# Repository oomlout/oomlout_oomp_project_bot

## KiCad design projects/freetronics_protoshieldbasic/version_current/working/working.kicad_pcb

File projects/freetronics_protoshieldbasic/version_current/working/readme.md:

# ProtoShieldBasic by freetronics  
This is a harvested standardized copy of a project from github.  
The original project can be found at:  
https://github.com/freetronics/ProtoShieldBasic  
Please consult that link for additional, details, files, and license information.  
Note: It was auto harvested and if the original repo had more than one board file or anything out of the ordinary the files here are likely not representative.

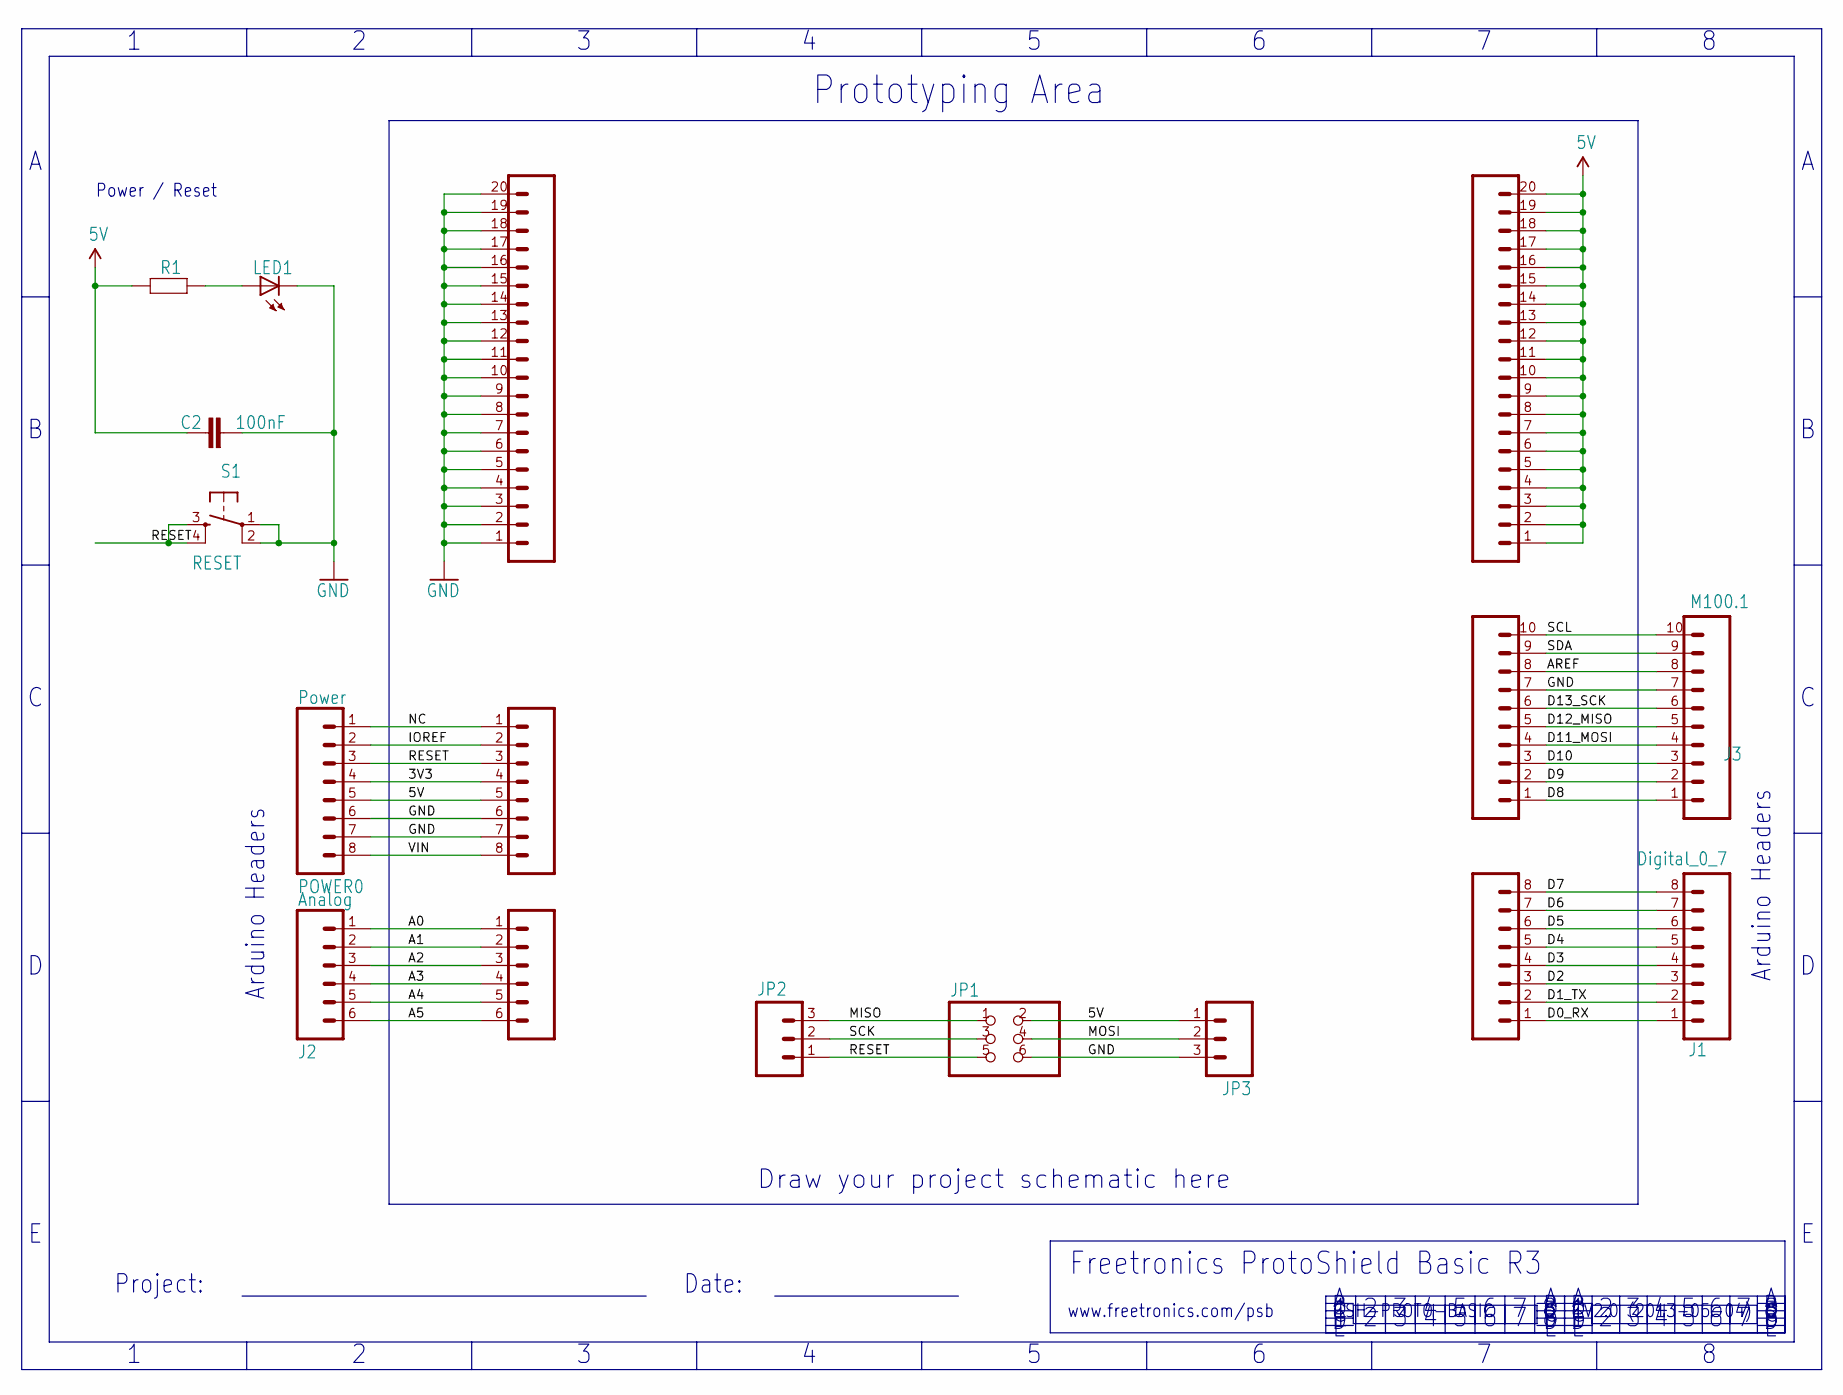
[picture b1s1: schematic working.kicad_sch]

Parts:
C2: 100nF; CAP-PTH-SMALL
J1: Digital_0_7; 1X08
J2: Analog; 1X06
J3: M100.1; 1X10
JP1: PINHD-2X3; 2X03
JP2, JP3: M03PTH; 1X03
LED1: LED3MM
PADS_5V0: M20; 1X20
PADS_GND0: M20; 1X20
POWER0: Power; 1X08
R1: RESISTORPTH1; AXIAL-0.3
S1: RESET; TACTILE-PTH
SL1: Digital_0_7; 1X08
SL2: Analog; 1X06
SL3: M100.1; 1X10
SLP0: Power; 1X08

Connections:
3V3: POWER0.4, SLP0.4
5V: C2.1, JP1.2, JP3.1, PADS_5V0.1, PADS_5V0.2, PADS_5V0.3, PADS_5V0.4, PADS_5V0.5, PADS_5V0.6, PADS_5V0.7, PADS_5V0.8, PADS_5V0.9, PADS_5V0.10, PADS_5V0.11, PADS_5V0.12, PADS_5V0.13, PADS_5V0.14, PADS_5V0.15, PADS_5V0.16, PADS_5V0.17, PADS_5V0.18, PADS_5V0.19, PADS_5V0.20, POWER0.5, R1.P$1 (1), SLP0.5
A0: J2.1, SL2.1
A1: J2.2, SL2.2
A2: J2.3, SL2.3
A3: J2.4, SL2.4
A4: J2.5, SL2.5
A5: J2.6, SL2.6
AREF: J3.8, SL3.8
D0_RX: J1.1, SL1.1
D1_TX: J1.2, SL1.2
D2: J1.3, SL1.3
D3: J1.4, SL1.4
D4: J1.5, SL1.5
D5: J1.6, SL1.6
D6: J1.7, SL1.7
D7: J1.8, SL1.8
D8: J3.1, SL3.1
D9: J3.2, SL3.2
D10: J3.3, SL3.3
D11_MOSI: J3.4, SL3.4
D12_MISO: J3.5, SL3.5
D13_SCK: J3.6, SL3.6
GND: C2.2, J3.7, JP1.6, JP3.3, LED1.K (C), PADS_GND0.1, PADS_GND0.2, PADS_GND0.3, PADS_GND0.4, PADS_GND0.5, PADS_GND0.6, PADS_GND0.7, PADS_GND0.8, PADS_GND0.9, PADS_GND0.10, PADS_GND0.11, PADS_GND0.12, PADS_GND0.13, PADS_GND0.14, PADS_GND0.15, PADS_GND0.16, PADS_GND0.17, PADS_GND0.18, PADS_GND0.19, PADS_GND0.20, POWER0.6, POWER0.7, S1.1, S1.2, SL3.7, SLP0.6, SLP0.7
IOREF: POWER0.2, SLP0.2
MISO: JP1.1, JP2.3
MOSI: JP1.4, JP3.2
unnamed: LED1.A, R1.P$2 (2)
NC: POWER0.1, SLP0.1
RESET: JP1.5, JP2.1, POWER0.3, S1.3, S1.4, SLP0.3
SCK: JP1.3, JP2.2
SCL: J3.10, SL3.10
SDA: J3.9, SL3.9
VIN: POWER0.8, SLP0.8

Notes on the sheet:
Date:
Prototyping Area
Project:
V2.0 (2013-05-04)
Arduino Headers
www.freetronics.com/psb
Draw your project schematic here
SH-PROTO-BASIC
Freetronics ProtoShield Basic R3
Power / Reset

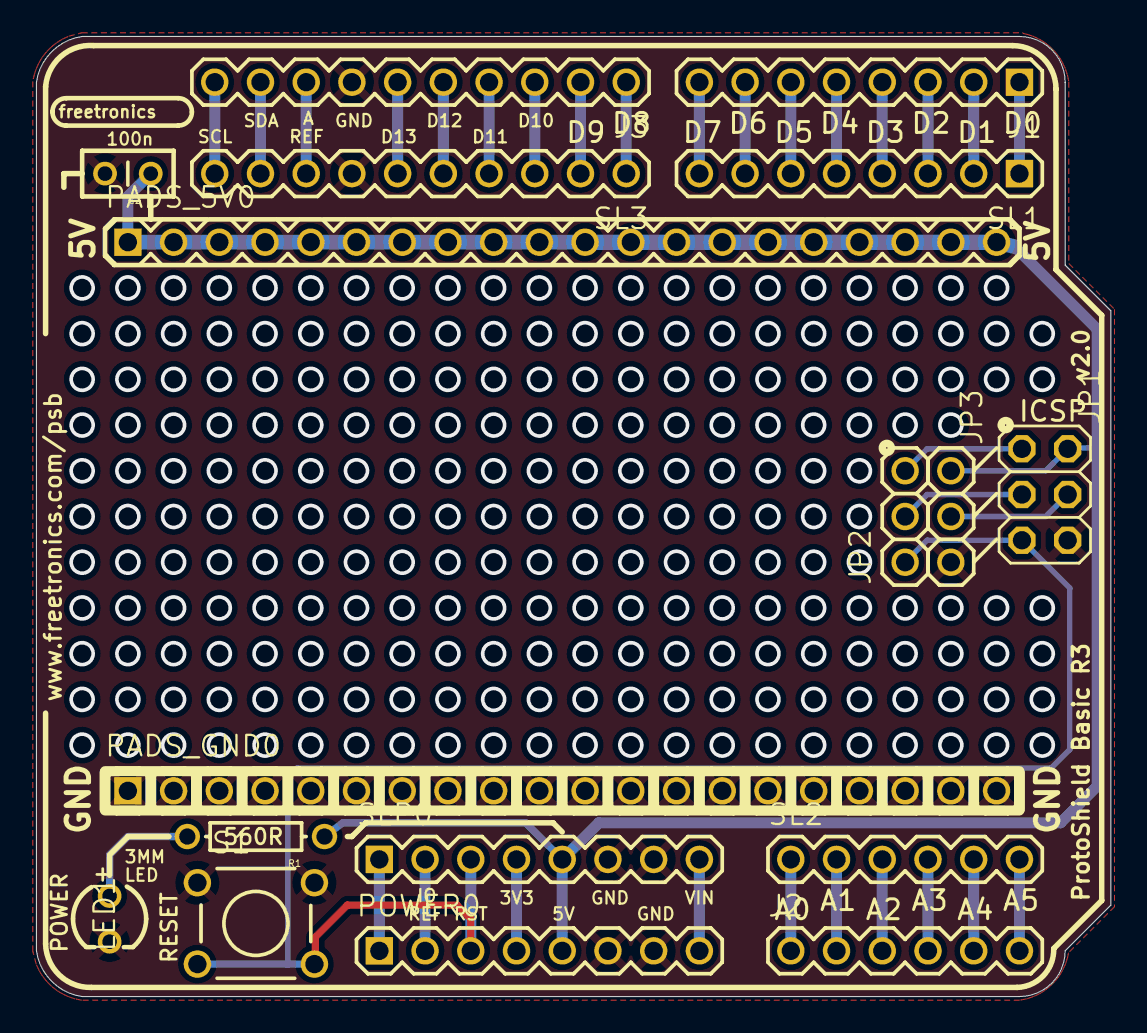
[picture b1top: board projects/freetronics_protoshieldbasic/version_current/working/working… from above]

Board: 2 copper layers, 59.7 x 53.3 mm, 17 parts (0 on the bottom side), 34 nets.

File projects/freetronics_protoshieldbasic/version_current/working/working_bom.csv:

"Id";"Designator";"Footprint";"Quantity";"Designation";"Supplier and ref";
1;"LED1";"LED3MM";1;"";;;
2;"SL2,J2";"1X06";2;"Analog";;;
3;"J1,SL1";"1X08";2;"Digital_0_7";;;
4;"PADS_GND0,PADS_5V0";"1X20";2;"M20";;;
5;"S1";"TACTILE-PTH";1;"RESET";;;
6;"SLP0,POWER0";"1X08";2;"Power";;;
7;"SL3,J3";"1X10";2;"Digital_8_13";;;
8;"C2";"CAP-PTH-SMALL";1;"100nF";;;
9;"JP3,JP2";"1X03";2;"";;;
10;"JP1";"2X03";1;"";;;
11;"R1";"AXIAL-0.3";1;"";;;

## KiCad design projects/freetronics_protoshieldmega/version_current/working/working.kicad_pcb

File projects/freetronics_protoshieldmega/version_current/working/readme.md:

# ProtoShieldMega by freetronics  
This is a harvested standardized copy of a project from github.  
The original project can be found at:  
https://github.com/freetronics/ProtoShieldMega  
Please consult that link for additional, details, files, and license information.  
Note: It was auto harvested and if the original repo had more than one board file or anything out of the ordinary the files here are likely not representative.

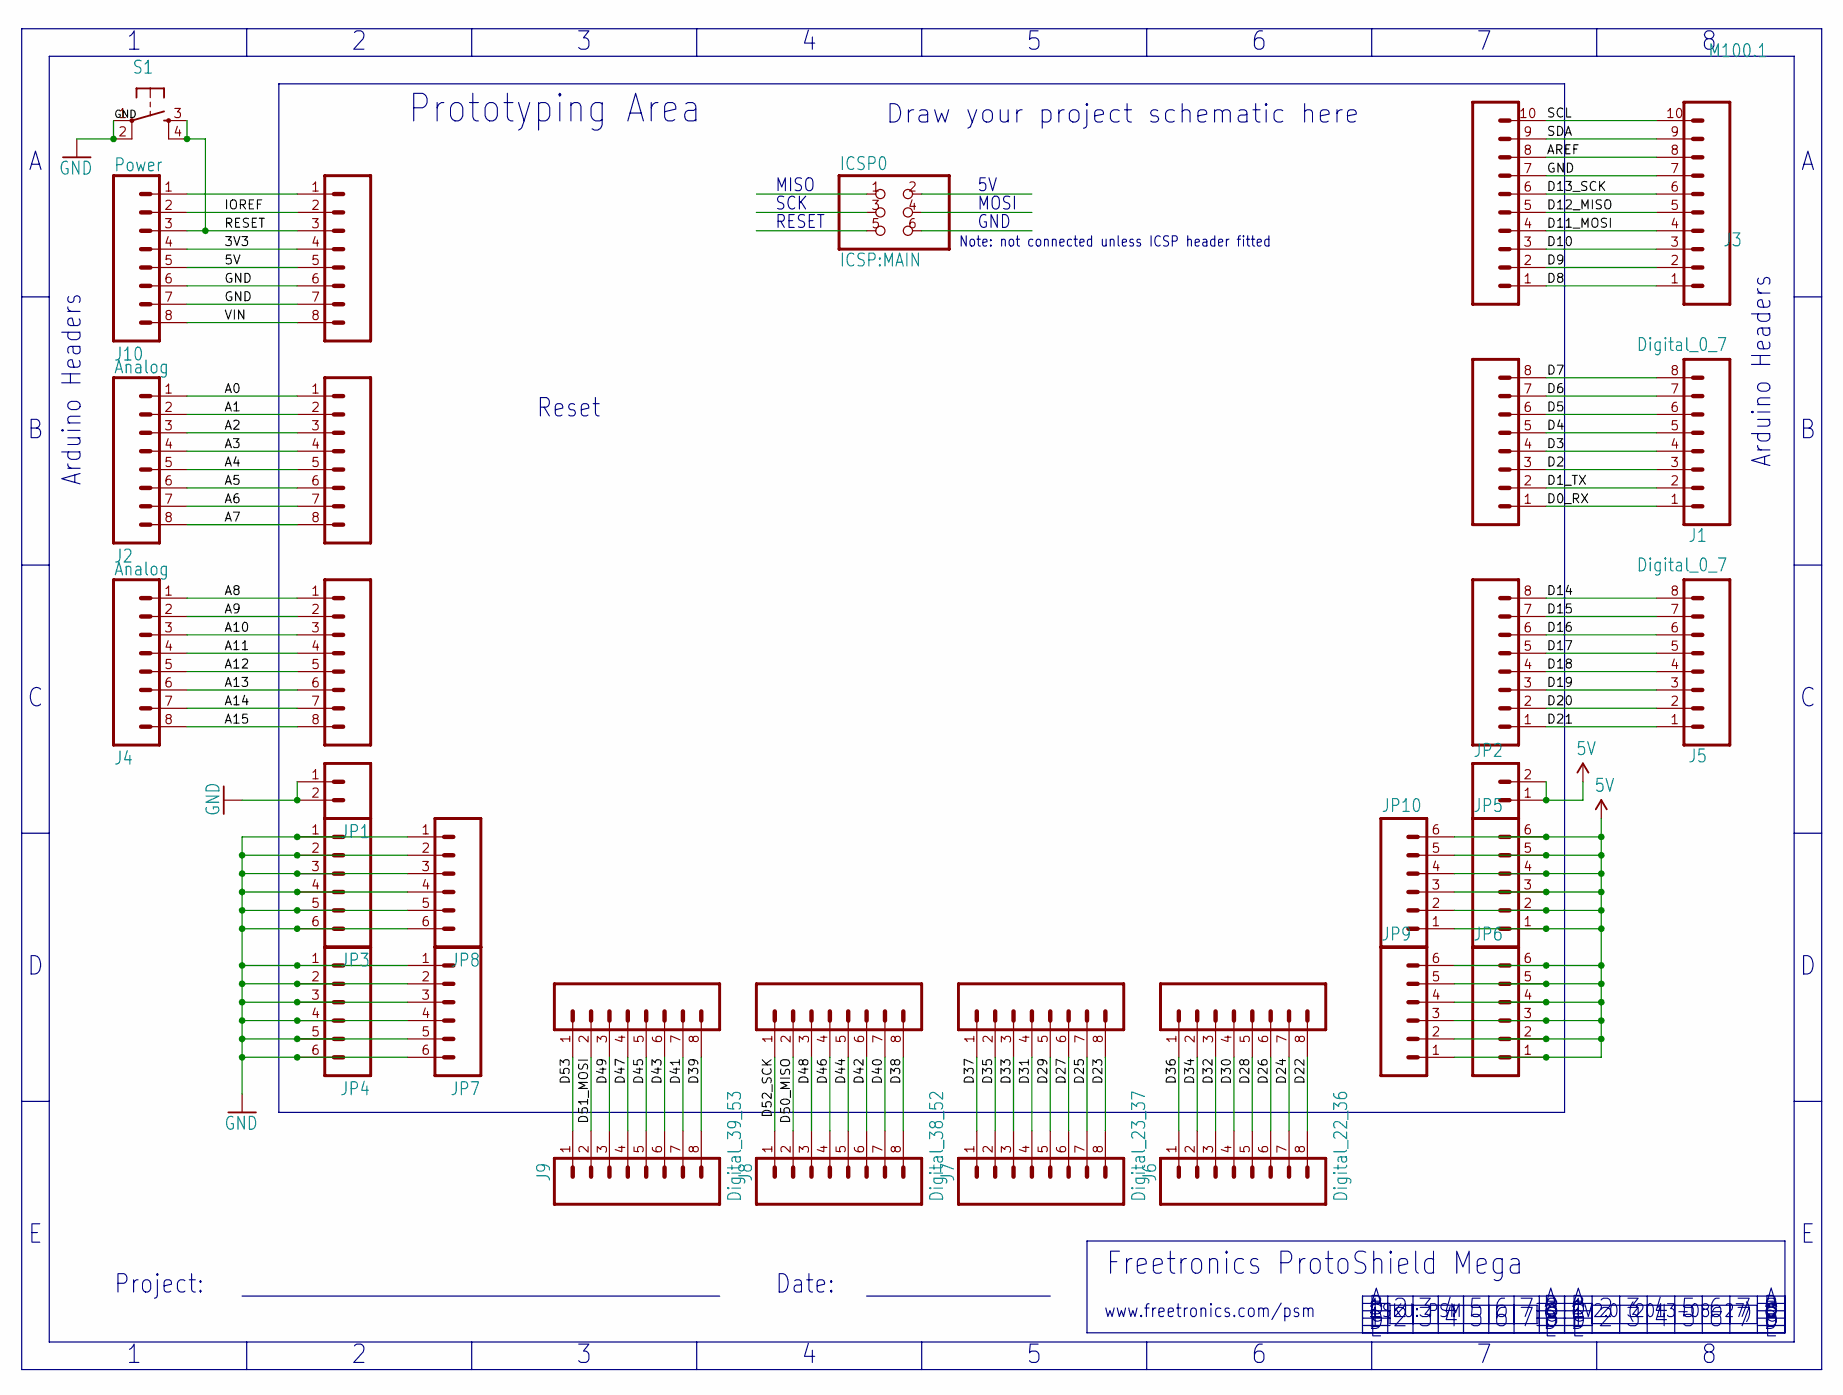
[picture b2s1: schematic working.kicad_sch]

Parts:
ICSP0: ICSP:MAIN; 2X03
J1, J5: Digital_0_7; 1X08
J2, J4: Analog; 1X08
J3: M100.1; 1X10
J6: Digital_22_36; 1X08
J7: Digital_23_37; 1X08
J8: Digital_38_52; 1X08
J9: Digital_39_53; 1X08
J10: Power; 1X08
JP1, JP2: M02PTH; 1X02
JP3, JP4, JP5, JP6, JP7, JP8, JP9, JP10: M06SIP; 1X06
S1: TAC_SWITCHPTH; TACTILE-PTH
SL1, SL5, SL6, SL7, SL8, SL9: Digital_0_7; 1X08
SL2, SL4: Analog; 1X08
SL3: M100.1; 1X10
SLP0: Power; 1X08

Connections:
3V3: J10.4, SLP0.4
5V: J10.5, JP2.1, JP2.2, JP5.1, JP5.2, JP5.3, JP5.4, JP5.5, JP5.6, JP6.1, JP6.2, JP6.3, JP6.4, JP6.5, JP6.6, JP9.1, JP9.2, JP9.3, JP9.4, JP9.5, JP9.6, JP10.1, JP10.2, JP10.3, JP10.4, JP10.5, JP10.6, SLP0.5
A0: J2.1, SL2.1
A1: J2.2, SL2.2
A2: J2.3, SL2.3
A3: J2.4, SL2.4
A4: J2.5, SL2.5
A5: J2.6, SL2.6
A6: J2.7, SL2.7
A7: J2.8, SL2.8
A8: J4.1, SL4.1
A9: J4.2, SL4.2
A10: J4.3, SL4.3
A11: J4.4, SL4.4
A12: J4.5, SL4.5
A13: J4.6, SL4.6
A14: J4.7, SL4.7
A15: J4.8, SL4.8
AREF: J3.8, SL3.8
D0_RX: J1.1, SL1.1
D1_TX: J1.2, SL1.2
D2: J1.3, SL1.3
D3: J1.4, SL1.4
D4: J1.5, SL1.5
D5: J1.6, SL1.6
D6: J1.7, SL1.7
D7: J1.8, SL1.8
D8: J3.1, SL3.1
D9: J3.2, SL3.2
D10: J3.3, SL3.3
D11_MOSI: J3.4, SL3.4
D12_MISO: J3.5, SL3.5
D13_SCK: J3.6, SL3.6
D14: J5.8, SL5.8
D15: J5.7, SL5.7
D16: J5.6, SL5.6
D17: J5.5, SL5.5
D18: J5.4, SL5.4
D19: J5.3, SL5.3
D20: J5.2, SL5.2
D21: J5.1, SL5.1
D22: J6.8, SL6.8
D23: J7.8, SL7.8
D24: J6.7, SL6.7
D25: J7.7, SL7.7
D26: J6.6, SL6.6
D27: J7.6, SL7.6
D28: J6.5, SL6.5
D29: J7.5, SL7.5
D30: J6.4, SL6.4
D31: J7.4, SL7.4
D32: J6.3, SL6.3
D33: J7.3, SL7.3
D34: J6.2, SL6.2
D35: J7.2, SL7.2
D36: J6.1, SL6.1
D37: J7.1, SL7.1
D38: J8.8, SL8.8
D39: J9.8, SL9.8
D40: J8.7, SL8.7
D41: J9.7, SL9.7
D42: J8.6, SL8.6
D43: J9.6, SL9.6
D44: J8.5, SL8.5
D45: J9.5, SL9.5
D46: J8.4, SL8.4
D47: J9.4, SL9.4
D48: J8.3, SL8.3
D49: J9.3, SL9.3
D50_MISO: J8.2, SL8.2
D51_MOSI: J9.2, SL9.2
D52_SCK: J8.1, SL8.1
D53: J9.1, SL9.1
GND: J3.7, J10.6, J10.7, JP1.1, JP1.2, JP3.1, JP3.2, JP3.3, JP3.4, JP3.5, JP3.6, JP4.1, JP4.2, JP4.3, JP4.4, JP4.5, JP4.6, JP7.1, JP7.2, JP7.3, JP7.4, JP7.5, JP7.6, JP8.1, JP8.2, JP8.3, JP8.4, JP8.5, JP8.6, S1.1, S1.2, SL3.7, SLP0.6, SLP0.7
IOREF: J10.2, SLP0.2
unnamed: J10.1, SLP0.1
RESET: J10.3, S1.3, S1.4, SLP0.3
SCL: J3.10, SL3.10
SDA: J3.9, SL3.9
VIN: J10.8, SLP0.8

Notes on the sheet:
www.freetronics.com/psm
V2.0 (2013-08-27)
Note: not connected unless ICSP header fitted
RESET
MISO
Arduino Headers
GND
Reset
Prototyping Area
Freetronics ProtoShield Mega
MOSI
SKU: PSM
Draw your project schematic here
Project:
SCK
Date:

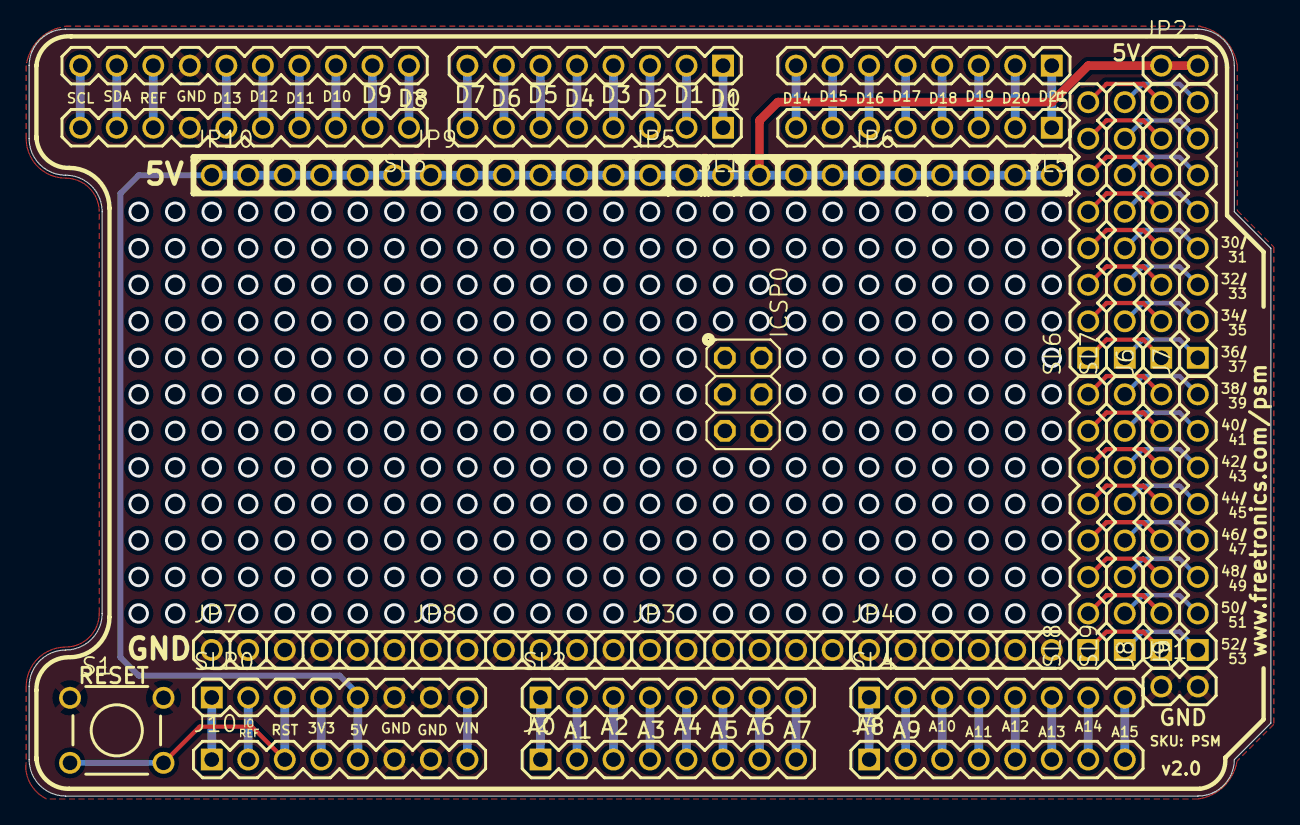
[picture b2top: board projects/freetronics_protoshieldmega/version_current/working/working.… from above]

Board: 2 copper layers, 86.4 x 53.3 mm, 32 parts (0 on the bottom side), 80 nets.

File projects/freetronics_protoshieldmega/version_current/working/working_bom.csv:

"Id";"Designator";"Footprint";"Quantity";"Designation";"Supplier and ref";
1;"JP4,JP9,JP5,JP8,JP6,JP10,JP7,JP3";"1X06";8;"";;;
2;"SL9,SL7,SL8,SL1,SL5,J5,J1,SL6";"1X08";8;"Digital_0_7";;;
3;"J2,J4,SL4,SL2";"1X08";4;"Analog";;;
4;"J3,SL3";"1X10";2;"Digital_8_13";;;
5;"S1";"TACTILE-PTH";1;"";;;
6;"ICSP0";"2X03";1;"ICSP:MAIN";;;
7;"J8";"1X08";1;"Digital_38_52";;;
8;"JP2,JP1";"1X02";2;"";;;
9;"J7";"1X08";1;"Digital_23_37";;;
10;"J9";"1X08";1;"Digital_39_53";;;
11;"SLP0,J10";"1X08";2;"Power";;;
12;"J6";"1X08";1;"Digital_22_36";;;

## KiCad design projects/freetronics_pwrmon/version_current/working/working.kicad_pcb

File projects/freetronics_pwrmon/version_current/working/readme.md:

# PWRMON by freetronics  
This is a harvested standardized copy of a project from github.  
The original project can be found at:  
https://github.com/freetronics/PWRMON  
Please consult that link for additional, details, files, and license information.  
Note: It was auto harvested and if the original repo had more than one board file or anything out of the ordinary the files here are likely not representative.

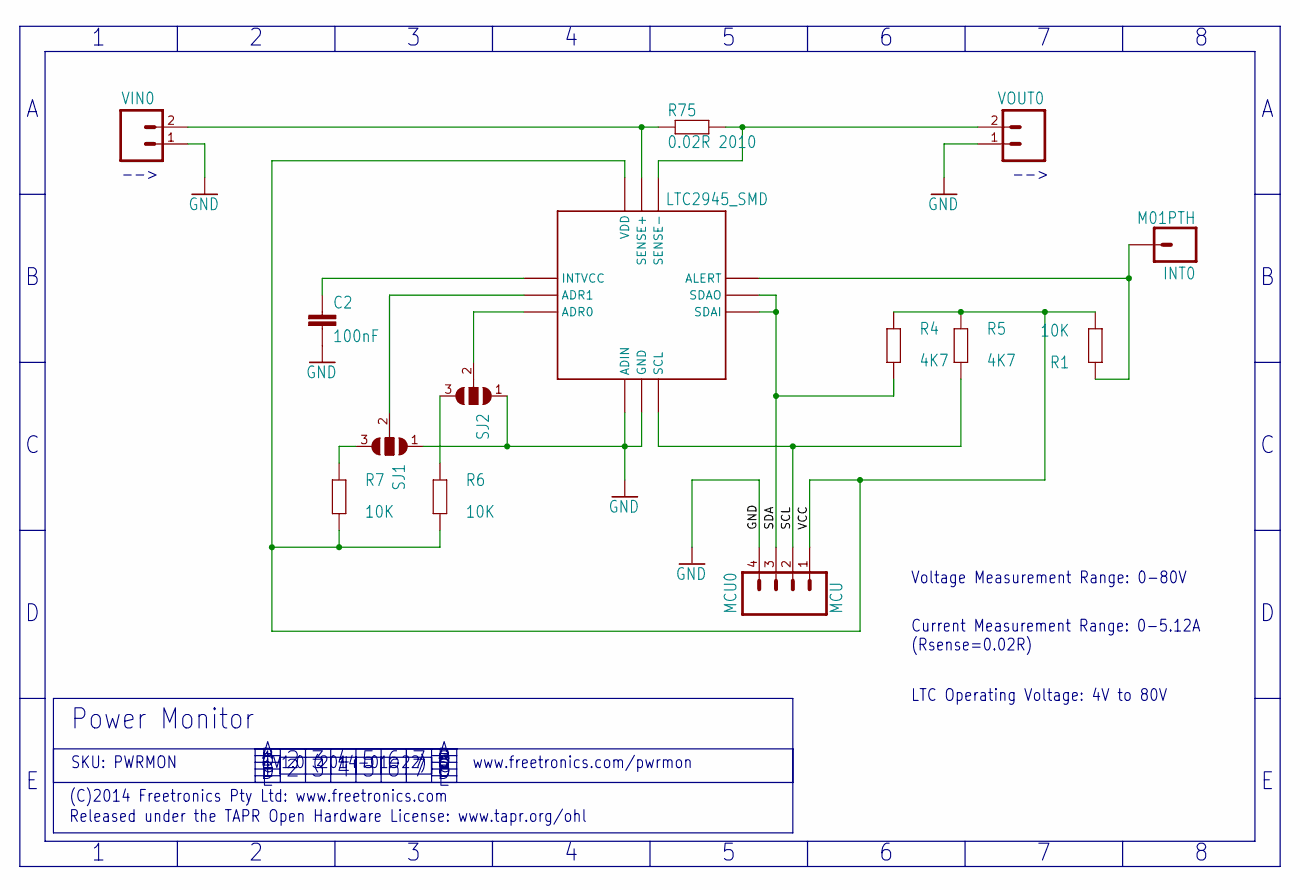
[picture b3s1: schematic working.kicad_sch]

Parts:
C2: 100nF; 0603
INT0: M01PTH; 1X01
LTC2945: LTC2945_SMD; QFN-12
MCU0: MCU; 1X04
R1, R6, R7: 10K; 0603
R4, R5: 4K7; 0603
R75: 0.02R 2010; R2010
SJ1, SJ2: SJ2W; SJ_2
VIN0: M02PTH; 1X02
VOUT0: M02PTH; 1X02

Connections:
GND: C2.2, LTC2945.4 (ADIN), LTC2945.5 (GND), MCU0.4, SJ1.1, SJ2.1, VIN0.1, VOUT0.1
unnamed: LTC2945.11 (SENSE+), R75.1, VIN0.2
unnamed: LTC2945.10 (SENSE-), R75.2, VOUT0.2
unnamed: LTC2945.2 (ADR1), SJ1.2
unnamed: INT0.1, LTC2945.9 (ALERT), R1.2
unnamed: C2.1, LTC2945.1 (INTVCC)
unnamed: LTC2945.3 (ADR0), SJ2.2
unnamed: R7.2, SJ1.3
unnamed: R6.2, SJ2.3
SCL: LTC2945.6 (SCL), MCU0.2, R5.1
SDA: LTC2945.7 (SDAI), LTC2945.8 (SDAO), MCU0.3, R4.1
VCC: LTC2945.12 (VDD), MCU0.1, R1.1, R4.2, R5.2, R6.1, R7.1

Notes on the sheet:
www.freetronics.com/pwrmon
Voltage Measurement Range: 0-80V
(C)2014 Freetronics Pty Ltd: www.freetronics.com
Power Monitor
Current Measurement Range: 0-5.12A (Rsense=0.02R)
SKU: PWRMON
Released under the TAPR Open Hardware License: www.tapr.org/ohl
-->
LTC Operating Voltage: 4V to 80V
V1.0 (2014-01-22)

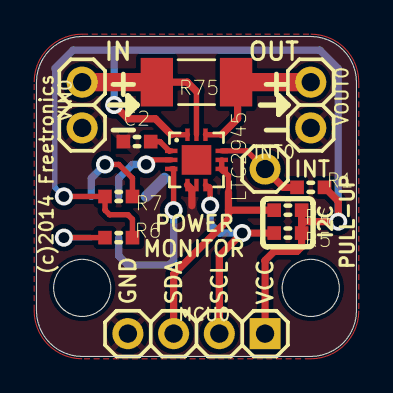
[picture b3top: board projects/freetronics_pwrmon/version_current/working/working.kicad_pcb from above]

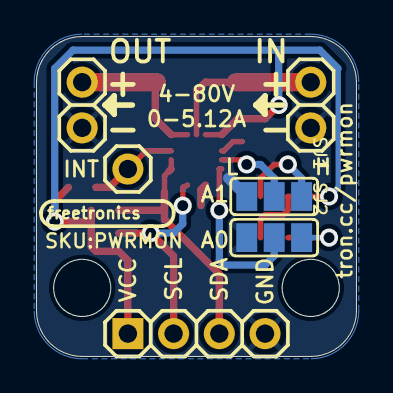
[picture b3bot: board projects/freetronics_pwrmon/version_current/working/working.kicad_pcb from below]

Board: 2 copper layers, 17.8 x 17.8 mm, 16 parts (2 on the bottom side), 12 nets.

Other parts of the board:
@HOLE0, @HOLE1: (no value)

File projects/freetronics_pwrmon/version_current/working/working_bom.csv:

"Id";"Designator";"Footprint";"Quantity";"Designation";"Supplier and ref";
1;"R7,R1,R6";"0603";3;"10K";;;
2;"C2";"0603";1;"100nF";;;
3;"@HOLE1,@HOLE0";"";2;"";;;
4;"INT0";"1X01";1;"M01PTH";;;
5;"VIN0,VOUT0";"1X02";2;"";;;
6;"R4,R5";"0603";2;"4K7";;;
7;"R75";"R2010";1;"0.02R 2010";;;
8;"MCU0";"1X04";1;"MCU";;;
9;"LTC2945";"QFN-12";1;"LTC2945_SMD";;;
10;"SJ2,SJ1";"SJ_2";2;"";;;

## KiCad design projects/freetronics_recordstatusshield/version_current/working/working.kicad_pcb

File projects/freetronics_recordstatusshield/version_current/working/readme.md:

# RecordStatusShield by freetronics  
This is a harvested standardized copy of a project from github.  
The original project can be found at:  
https://github.com/freetronics/RecordStatusShield  
Please consult that link for additional, details, files, and license information.  
Note: It was auto harvested and if the original repo had more than one board file or anything out of the ordinary the files here are likely not representative.

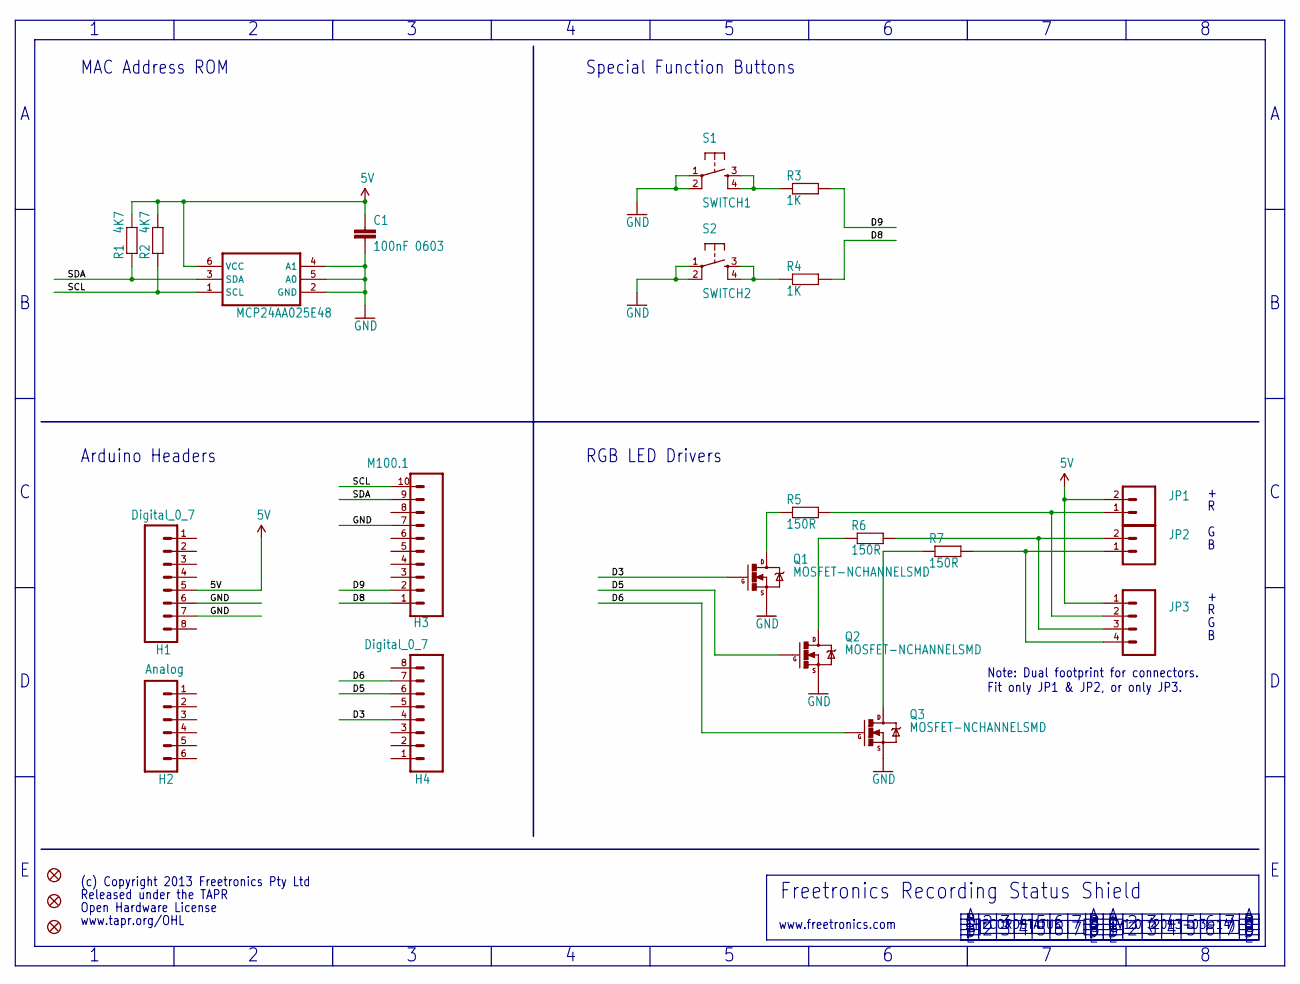
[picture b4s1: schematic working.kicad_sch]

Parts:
C1: 100nF 0603; C0603
FID5, FID6, FID7: FIDUCIAL1X2.5; FIDUCIAL-1X2.5
H1, H4: Digital_0_7; 1X08
H2: Analog; 1X06
H3: M100.1; 1X10
IC1: MCP24AA025E48; SOT23-6
JP1, JP2: M025MM; SCREWTERMINAL-5MM-2
JP3: M04PTH; 1X04
Q1, Q2, Q3: MOSFET-NCHANNELSMD; SOT23-3
R1, R2: 4K7; 0603
R3, R4: 1K; 0603
R5, R6, R7: 150R; 0603
S1: SWITCH1; TACTILE-PTH
S2: SWITCH2; TACTILE-PTH

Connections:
5V: C1.1, H1.5, IC1.6 (VCC), JP1.2, JP3.1, R1.2, R2.2
D3: H4.4, Q1.1 (G)
D5: H4.6, Q2.1 (G)
D6: H4.7, Q3.1 (G)
D8: H3.1, R4.2
D9: H3.2, R3.2
GND: C1.2, H1.6, H1.7, H3.7, IC1.2 (GND), IC1.4 (A1), IC1.5 (A0), Q1.2 (S), Q2.2 (S), Q3.2 (S), S1.1, S1.2, S2.1, S2.2
unnamed: R3.1, S1.3, S1.4
unnamed: R4.1, S2.3, S2.4
unnamed: JP2.1, JP3.4, R7.2
unnamed: JP2.2, JP3.3, R6.2
unnamed: JP1.1, JP3.2, R5.2
unnamed: Q1.3 (D), R5.1
unnamed: Q2.3 (D), R6.1
unnamed: Q3.3 (D), R7.1
SCL: H3.10, IC1.1 (SCL), R2.1
SDA: H3.9, IC1.3 (SDA), R1.1

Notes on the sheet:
Special Function Buttons
V1.0 (2013-03-14)
www.freetronics.com
Open Hardware License
Note: Dual footprint for connectors. Fit only JP1 & JP2, or only JP3.
Arduino Headers
(c) Copyright 2013 Freetronics Pty Ltd
Released under the TAPR
RECORDSTATUS
MAC Address ROM
Freetronics Recording Status Shield
RGB LED Drivers
www.tapr.org/OHL

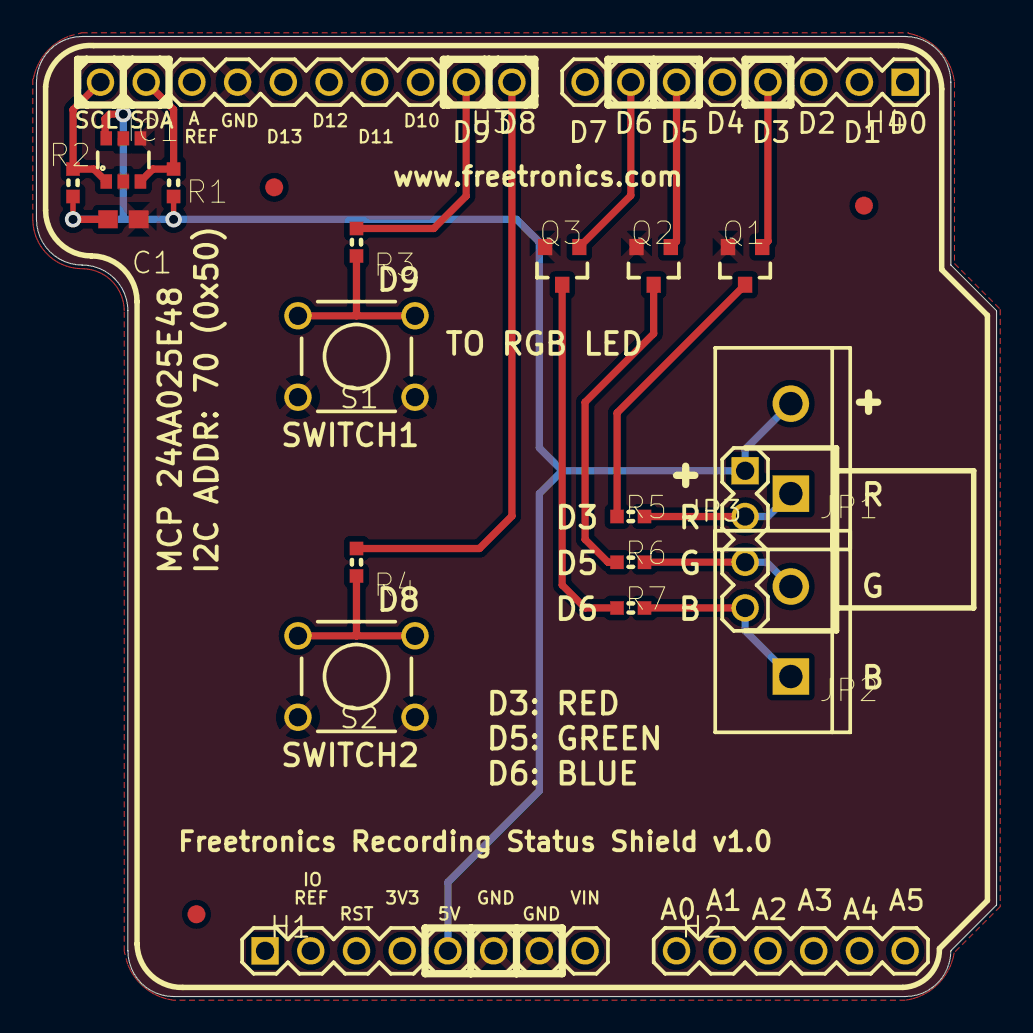
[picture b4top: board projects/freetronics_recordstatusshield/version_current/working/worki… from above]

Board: 2 copper layers, 53.3 x 53.3 mm, 24 parts (0 on the bottom side), 17 nets.

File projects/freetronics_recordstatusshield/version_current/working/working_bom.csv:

"Id";"Designator";"Footprint";"Quantity";"Designation";"Supplier and ref";
1;"R5,R6,R7";"0603";3;"150R";;;
2;"R1,R2";"0603";2;"4K7";;;
3;"Q3,Q2,Q1";"SOT23-3";3;"2N7002";;;
4;"IC1";"SOT23-6";1;"MCP24AA025E48";;;
5;"C1";"C0603";1;"100nF 0603";;;
6;"JP2,JP1";"SCREWTERMINAL-5MM-2";2;"";;;
7;"FID6,FID5,FID7";"FIDUCIAL-1X2.5";3;"FIDUCIAL1X2.5";;;
8;"H4,H1";"1X08";2;"Digital_0_7";;;
9;"R4,R3";"0603";2;"1K";;;
10;"S2";"TACTILE-PTH";1;"SWITCH2";;;
11;"H3";"1X10";1;"Digital_8_13";;;
12;"S1";"TACTILE-PTH";1;"SWITCH1";;;
13;"H2";"1X06";1;"Analog";;;
14;"JP3";"1X04";1;"";;;

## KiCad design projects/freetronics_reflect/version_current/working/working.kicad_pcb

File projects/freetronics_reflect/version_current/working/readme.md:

# REFLECT by freetronics  
This is a harvested standardized copy of a project from github.  
The original project can be found at:  
https://github.com/freetronics/REFLECT  
Please consult that link for additional, details, files, and license information.  
Note: It was auto harvested and if the original repo had more than one board file or anything out of the ordinary the files here are likely not representative.

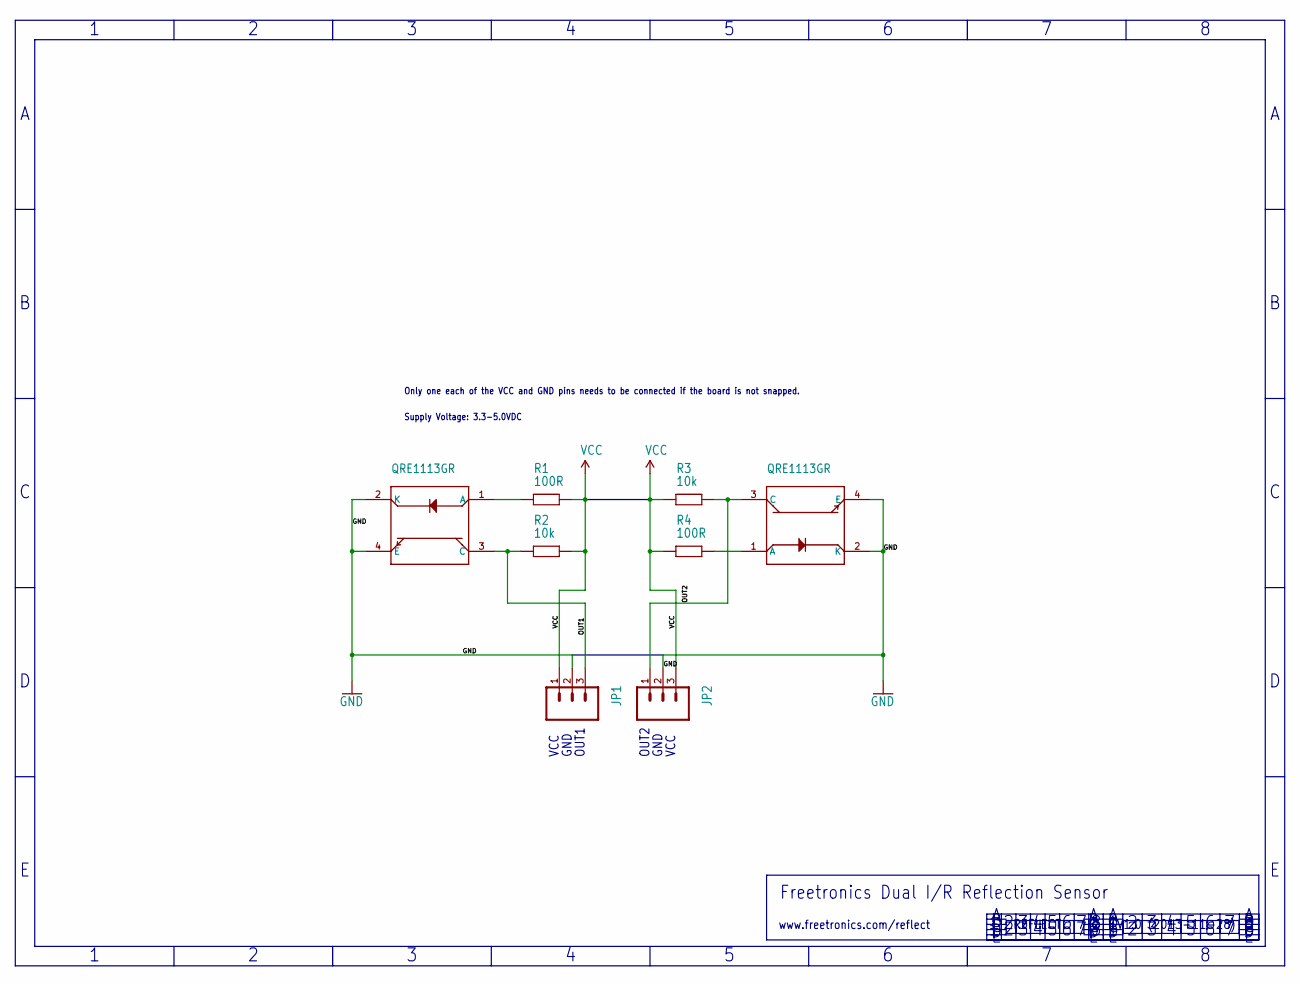
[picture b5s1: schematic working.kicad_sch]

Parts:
IC1, IC2: QRE1113GR
JP1, JP2: M03PTH; 1X03
R1, R4: 100R; 0603
R2, R3: 10k; 0603

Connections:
GND: IC1.2 (K), IC1.4 (E), IC2.2 (K), IC2.4 (E), JP1.2, JP2.2
unnamed: IC1.1 (A), R1.1
unnamed: IC2.1 (A), R4.2
OUT1: IC1.3 (C), JP1.3, R2.1
OUT2: IC2.3 (C), JP2.1, R3.2
VCC: JP1.1, JP2.3, R1.2, R2.2, R3.1, R4.1

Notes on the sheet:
OUT2
GND
REFLECT
Freetronics Dual I/R Reflection Sensor
OUT1
www.freetronics.com/reflect
VCC
V1.0 (2013-11-28)
Only one each of the VCC and GND pins needs to be connected if the board is not snapped.
Supply Voltage: 3.3-5.0VDC

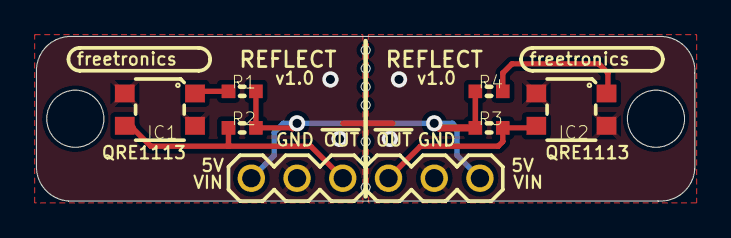
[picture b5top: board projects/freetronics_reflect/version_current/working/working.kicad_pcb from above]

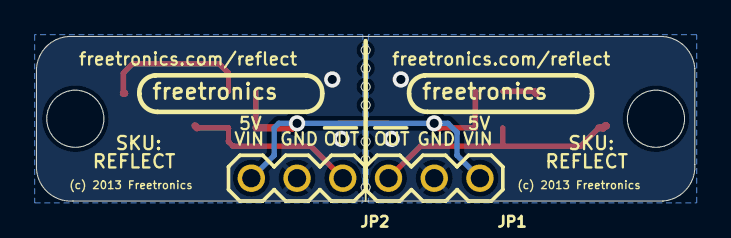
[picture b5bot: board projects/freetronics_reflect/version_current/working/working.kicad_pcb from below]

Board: 2 copper layers, 36.6 x 9.1 mm, 17 parts (2 on the bottom side), 6 nets.

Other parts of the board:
@HOLE0, @HOLE1, @HOLE2, @HOLE3, @HOLE4, @HOLE5, @HOLE6, @HOLE7, @HOLE8: (no value)

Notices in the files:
projects/freetronics_protoshieldbasic/version_current/working/working.kicad_pcb:
(c) 2013 Freetronics
projects/freetronics_protoshieldmega/version_current/working/working.kicad_pcb:
(C) 2013
projects/freetronics_recordstatusshield/version_current/working/working.kicad_pcb:
(c) 2013 Freetronics Pty Ltd
projects/freetronics_relay16mega/version_current/working/working.kicad_pcb:
(c) 2012-14 Freetronics Pty Ltd
Hardware License: tapr.org/OHL
